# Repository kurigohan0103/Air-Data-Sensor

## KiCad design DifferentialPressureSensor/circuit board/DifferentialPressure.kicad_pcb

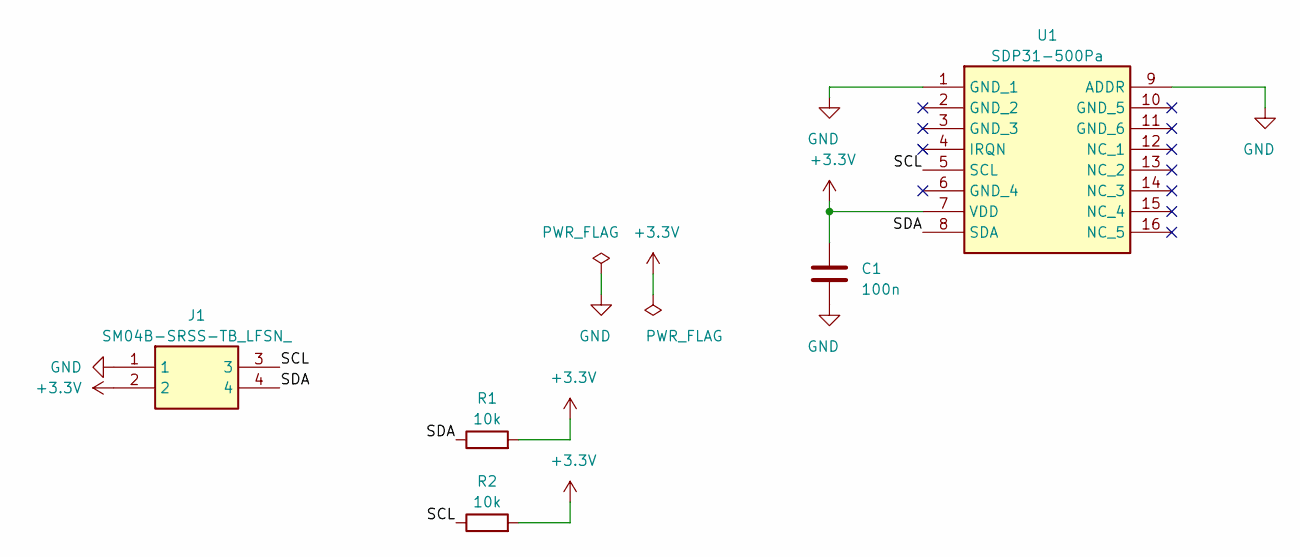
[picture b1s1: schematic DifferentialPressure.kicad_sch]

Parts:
C1: 100n; C_0603_1608Metric
J1: SM04B-SRSS-TB_LFSN_; Manufacturer_Part_Number SM04B-SRSS-TB(LFSN)
R1, R2: 10k; R_0603_1608Metric
U1: SDP31-500Pa; SDP31-500PA; Manufacturer_Part_Number SDP31-500Pa; Mouser Part Number 403-SDP31-500PA

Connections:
+3.3V: C1.1, J1.2, R1.2, R2.2, U1.7 (VDD)
/SCL: J1.3, R2.1, U1.5 (SCL)
/SDA: J1.4, R1.1, U1.8 (SDA)
GND: C1.2, J1.1, U1.1 (GND_1), U1.9 (ADDR)

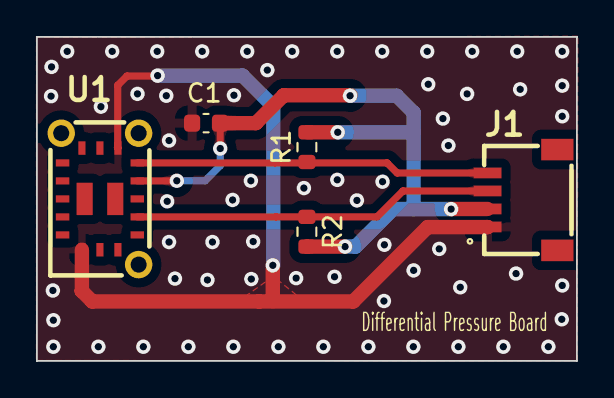
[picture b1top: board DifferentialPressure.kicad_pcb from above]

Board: 2 copper layers, 30.0 x 18.0 mm, 5 parts (0 on the bottom side), 4 nets.
